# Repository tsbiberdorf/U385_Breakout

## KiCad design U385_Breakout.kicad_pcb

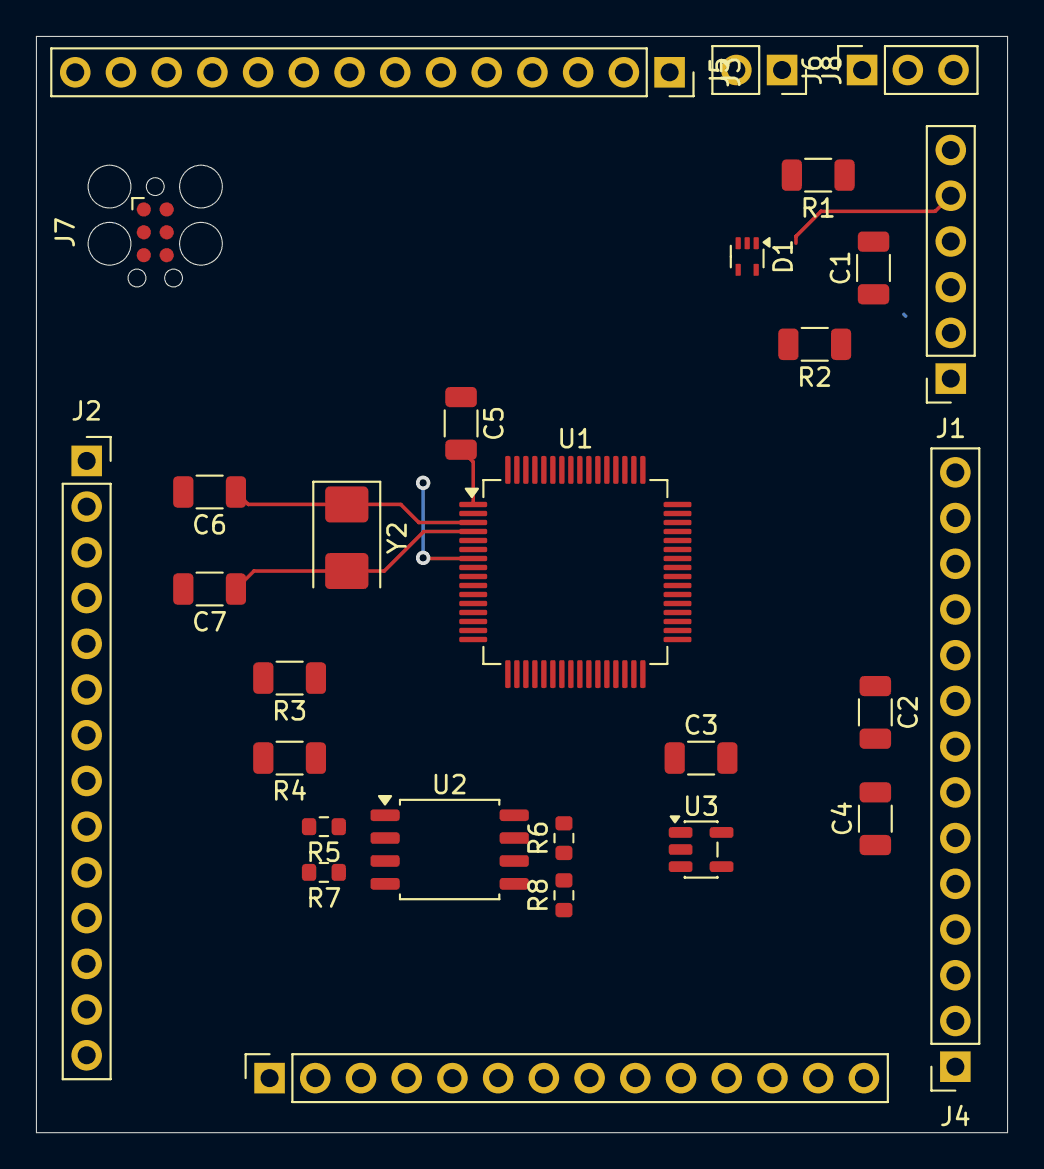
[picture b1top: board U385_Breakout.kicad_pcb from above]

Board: 2 copper layers, 54.0 x 60.9 mm, 28 parts (0 on the bottom side), 65 nets.

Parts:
C1: 4.7uF; R_1206_3216Metric
C2, C5: 100nF; R_1206_3216Metric
C3, C4: 1uF; R_1206_3216Metric
C6, C7: 8.2pF; R_1206_3216Metric
D1: TPD2E001DRLR; Texas_R-PDSO-N5_DRL-5
J1: Conn_01x06_Socket; PinSocket_1x06_P2.54mm_Vertical
J2, J3, J4, J5: Conn_01x14_Socket; PinSocket_1x14_P2.54mm_Vertical
J6: Conn_01x03_Socket; PinSocket_1x03_P2.54mm_Vertical
J7: Conn_ARM_SWD_TagConnect_TC2030; Tag-Connect_TC2030-IDC-FP_2x03_P1.27mm_Vertical
J8: Conn_01x02_Socket; PinSocket_1x02_P2.54mm_Vertical
R1, R2: 5.1K; R_1206_3216Metric
R3, R4: 100K; R_1206_3216Metric
R5, R6, R7, R8: 0; R_0603_1608Metric
U1: STM32U385RGT6; LQFP-64_10x10mm_P0.5mm
U2: W25Q128JVS; SOIC-8_5.3x5.3mm_P1.27mm
U3: LP5907MFX-3.3; SOT-23-5
Y2: 32.768Khz; Crystal_SMD_5032-2Pin_5.0x3.2mm

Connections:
/D+: D1.3 (IO1), J1.5, U1.45 (PA12)
/D-: D1.5 (IO2), J1.4, U1.44 (PA11)
/NRST: J2.5, J7.3 (~RESET), U1.7 (NRST)
/PA0_14: J2.10, U1.14 (PA0)
/PA1_15: J2.11, U1.15 (PA1)
/PA1_27: J3.9, U1.27 (PB1)
/PA2_16: J2.12, U1.16 (PA2)
/PA3_17: J2.13, U1.17 (PA3)
/PA4_20: J3.2, R5.2, U1.20 (PA4)
/PA5_21: J3.3, R6.2, U1.21 (PA5)
/PA6_22: J3.4, R7.2, U1.22 (PA6)
/PA7_23: J3.5, R8.2, U1.23 (PA7)
/PA8_41: J4.9, U1.41 (PA8)
/PA9_42: J4.10, U1.42 (PA9)
/PA10_43: J4.11, U1.43 (PA10)
/PA15_50: J5.2, U1.50 (PA15)
/PB0_26: J3.8, U1.26 (PB0)
/PB2_28: J3.10, U1.28 (PB2)
/PB4_56: J5.7, U1.56 (PB4)
/PB5_57: J5.8, U1.57 (PB5)
/PB6_58: J5.9, U1.58 (PB6)
/PB7_59: J5.10, U1.59 (PB7)
/PB8_61: J5.12, U1.61 (PB8)
/PB9_62: J5.13, U1.62 (PB9)
/PB10_29: J3.11, U1.29 (PB10)
/PB12_33: J3.12, U1.33 (PB12)
/PB13_34: J4.2, U1.34 (PB13)
/PB14_35: J4.3, U1.35 (PB14)
/PB15_36: J4.4, U1.36 (PB15)
/PC0_8: J2.6, U1.8 (PC0)
/PC1_9: J2.7, U1.9 (PC1)
/PC2_10: J2.8, U1.10 (PC2)
/PC3_11: J2.9, U1.11 (PC3)
/PC4_24: J3.6, U1.24 (PC4)
/PC5_25: J3.7, U1.25 (PC5)
/PC6_37: J4.5, U1.37 (PC6)
/PC7_38: J4.6, U1.38 (PC7)
/PC8_39: J4.7, U1.39 (PC8)
/PC9_40: J4.8, U1.40 (PC9)
/PC10_51: J5.3, U1.51 (PC10)
/PC11_52: J5.4, U1.52 (PC11)
/PC12_53: J5.5, U1.53 (PC12)
/PC13_2: J2.2, U1.2 (PC13)
/PD2_54: J5.6, U1.54 (PD2)
/PH0_5: J2.3, U1.5 (PH0-OSC_IN)
/PH1_6: J2.4, U1.6 (PH1-OSC_OUT)
/PH3_BOOT0_6: J5.11, U1.60 (PH3-BOOT0)
/PowerSheet/Vbat: J6.1, J8.2
/PowerSheet/Vin: C3.1, J6.2, R3.2, U3.1 (IN), U3.3 (EN)
/PowerSheet/Vusb: C1.2, D1.1 (VCC), J1.1, J6.3
/SWCLK: J7.4 (SWCLK), U1.49 (PA14)
/SWDIO: J7.2 (SWDIO), U1.46 (PA13)
/SWO: J7.6 (SWO), U1.55 (PB3)
/V3.3: C2.2, C4.1, J2.14, J7.1 (VCC), U1.13 (VDDA), U1.19 (VDD), U1.32 (VDD), U1.48 (VDDUSB), U1.64 (VDD), U2.8 (VCC), U3.5 (OUT)
GND: C1.1, C2.1, C3.2, C4.2, C5.1, C6.2, C7.2, D1.4 (GND), J1.2, J2.1, J3.1, J3.13, J3.14, J4.1, J4.12, J4.13, J4.14, J5.1, J5.14, J7.5 (GND), J8.1, R1.2, R2.2, R4.2, U1.12 (VSSA), U1.18 (VSS), U1.31 (VSS), U1.47 (VSS), U1.63 (VSS), U2.4 (GND), U3.2 (GND)
unnamed: J1.3, R2.1
unnamed: J1.6, R1.1
unnamed: C6.1, U1.3 (PC14-OSC32_IN), Y2.1
unnamed: C7.1, U1.4 (PC15-OSC32_OUT), Y2.2
unnamed: C5.2, R3.1, R4.1, U1.1 (VBAT), U1.30 (VCAP)
unnamed: R6.1, U2.6 (CLK)
unnamed: R8.1, U2.5 (DI/IO_{0})
unnamed: R7.1, U2.2 (DO/IO_{1})
unnamed: R5.1, U2.1 (~CS)
unnamed: U2.3 (~WP/IO_{2}), U2.7 (~HOLD/~RESET/IO_{3})
